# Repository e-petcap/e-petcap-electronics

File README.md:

# e-petcap-electronics
a e-petcap electronics

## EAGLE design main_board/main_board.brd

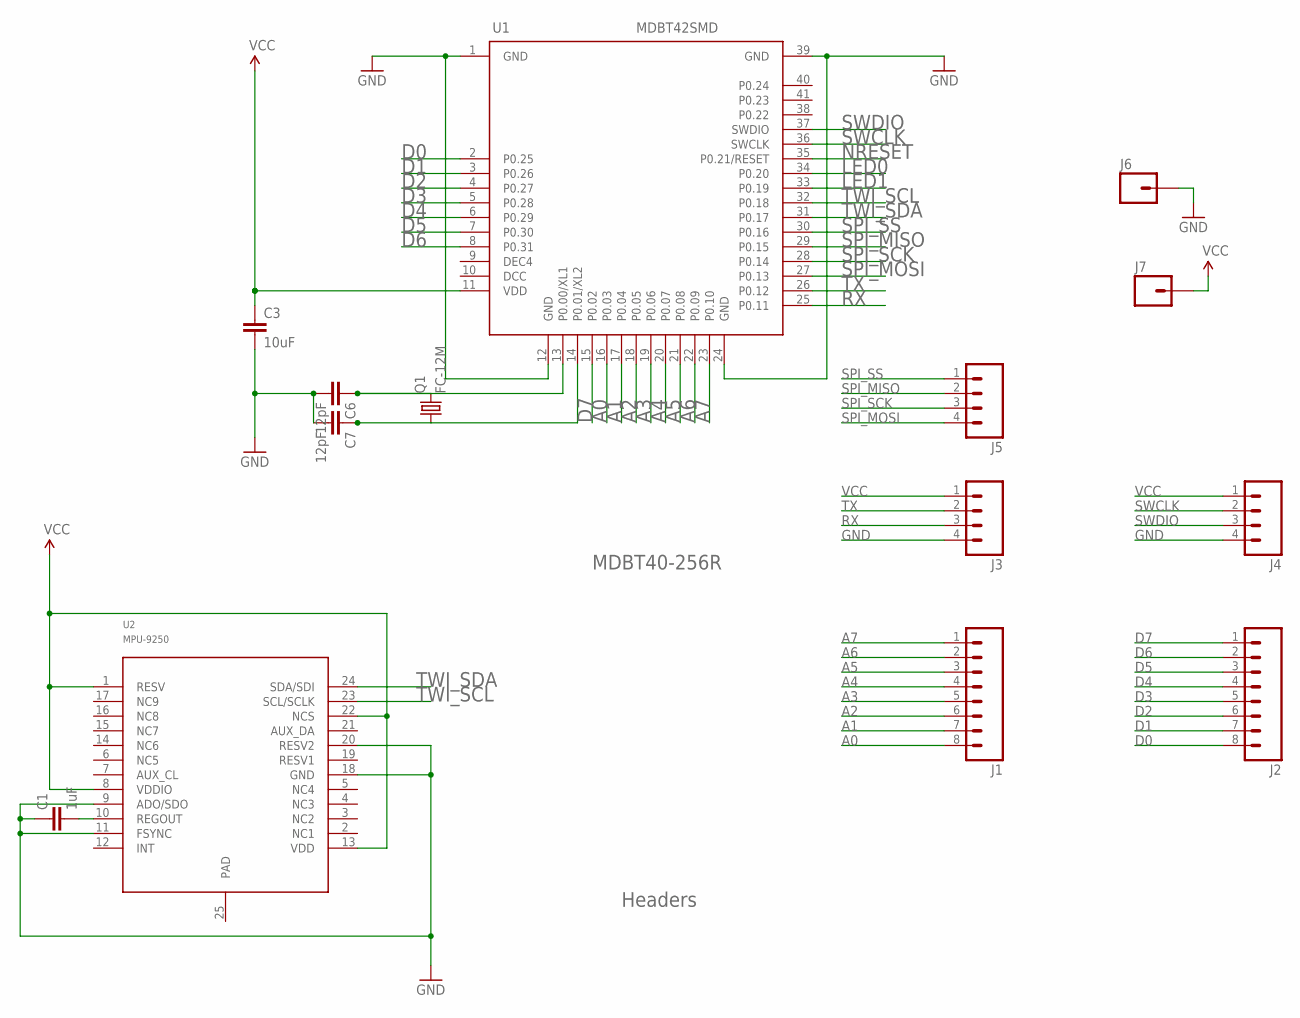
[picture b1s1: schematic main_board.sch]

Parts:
C1: 1uF; 0603-CAP
C3: 10uF; 0603-CAP
C6, C7: 12pF; 0603-CAP
J1, J2: M08SILK_FEMALE_PTH; 1X08
J3, J4, J5: M04PTH; 1X04
J6, J7: M01_SMDSMD_4X2; 1X01_SMD
Q1: FC-12M
U1: MDBT42SMD; MDBT42
U2: MPU-9250; LEAD-QFN24

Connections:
A0: J1.8, U1.16 (P0.03)
A1: J1.7, U1.17 (P0.04)
A2: J1.6, U1.18 (P0.05)
A3: J1.5, U1.19 (P0.06)
A4: J1.4, U1.20 (P0.07)
A5: J1.3, U1.21 (P0.08)
A6: J1.2, U1.22 (P0.09)
A7: J1.1, U1.23 (P0.10)
D0: J2.8, U1.2 (P0.25)
D1: J2.7, U1.3 (P0.26)
D2: J2.6, U1.4 (P0.27)
D3: J2.5, U1.5 (P0.28)
D4: J2.4, U1.6 (P0.29)
D5: J2.3, U1.7 (P0.30)
D6: J2.2, U1.8 (P0.31)
D7: J2.1, U1.15 (P0.02)
GND: C1.1, C3.2, C6.2, C7.2, J3.4, J4.4, J6.P$1, U1.1 (GND), U1.12 (GND), U1.24 (GND), U1.39 (GND), U2.9 (ADO/SDO), U2.11 (FSYNC), U2.18 (GND), U2.20 (RESV2)
LED0: U1.34 (P0.20)
LED1: U1.33 (P0.19)
unnamed: C7.1, Q1.1, U1.14 (P0.01/XL2)
unnamed: C6.1, Q1.2, U1.13 (P0.00/XL1)
unnamed: C1.2, U2.10 (REGOUT)
NRESET: U1.35 (P0.21/RESET)
RX: J3.3, U1.25 (P0.11)
SPI_MISO: J5.2, U1.29 (P0.15)
SPI_MOSI: J5.4, U1.27 (P0.13)
SPI_SCK: J5.3, U1.28 (P0.14)
SPI_SS: J5.1, U1.30 (P0.16)
SWCLK: J4.2, U1.36 (SWCLK)
SWDIO: J4.3, U1.37 (SWDIO)
TWI_SCL: U1.32 (P0.18), U2.23 (SCL/SCLK)
TWI_SDA: U1.31 (P0.17), U2.24 (SDA/SDI)
TX: J3.2, U1.26 (P0.12)
VCC: C3.1, J3.1, J4.1, J7.P$1, U1.11 (VDD), U2.1 (RESV), U2.8 (VDDIO), U2.13 (VDD), U2.22 (NCS)

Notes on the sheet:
Headers
MDBT40-256R

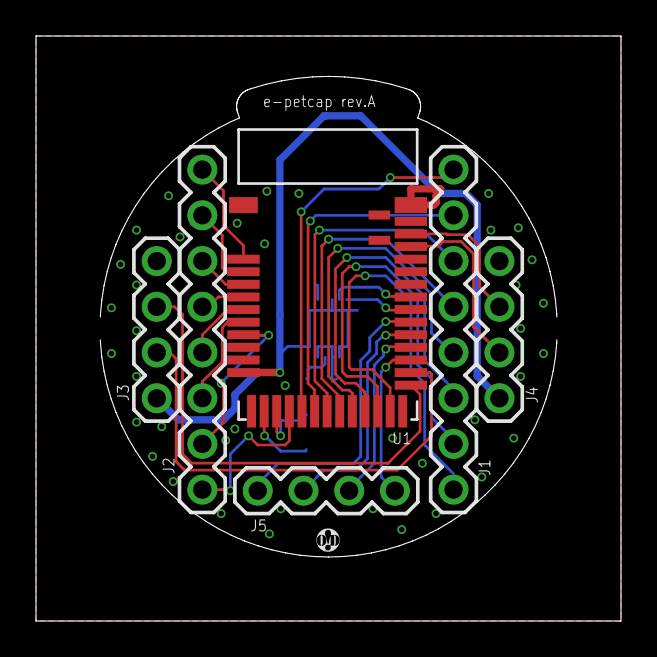
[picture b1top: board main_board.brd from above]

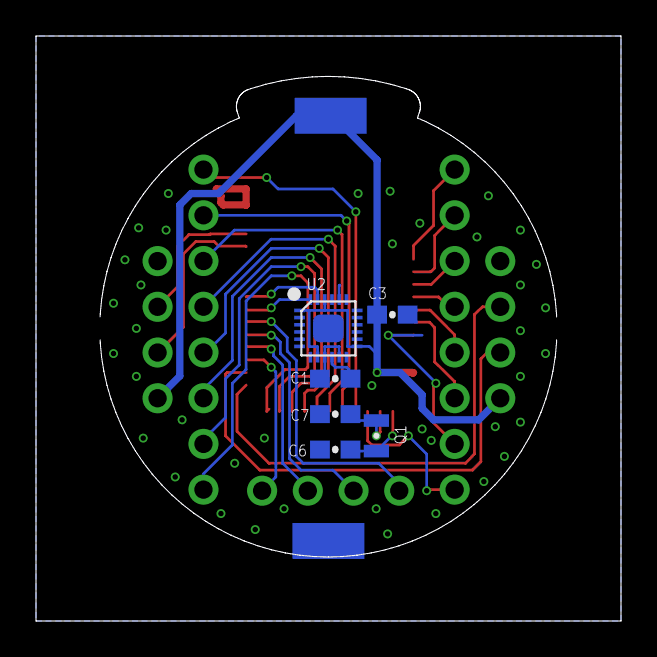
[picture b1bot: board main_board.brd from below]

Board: 4 copper layers, 32.5 x 32.5 mm, 14 parts (8 on the bottom side), 31 nets.

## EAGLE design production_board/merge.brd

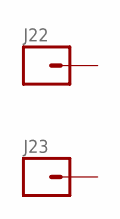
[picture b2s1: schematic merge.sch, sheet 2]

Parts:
J22, J23: M01; 1X01_BIG

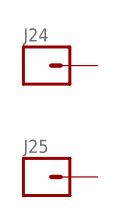
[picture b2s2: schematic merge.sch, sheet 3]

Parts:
J24, J25: M01; 1X01_BIG

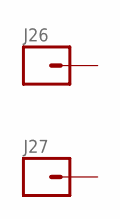
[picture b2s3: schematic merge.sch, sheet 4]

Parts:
J26, J27: M01; 1X01_BIG

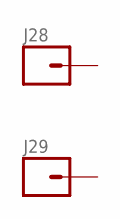
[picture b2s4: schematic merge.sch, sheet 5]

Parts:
J28, J29: M01; 1X01_BIG

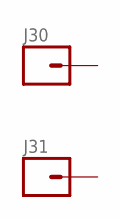
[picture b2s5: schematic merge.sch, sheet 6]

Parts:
J30, J31: M01; 1X01_BIG

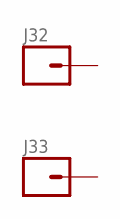
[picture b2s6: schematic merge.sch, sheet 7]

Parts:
J32, J33: M01; 1X01_BIG

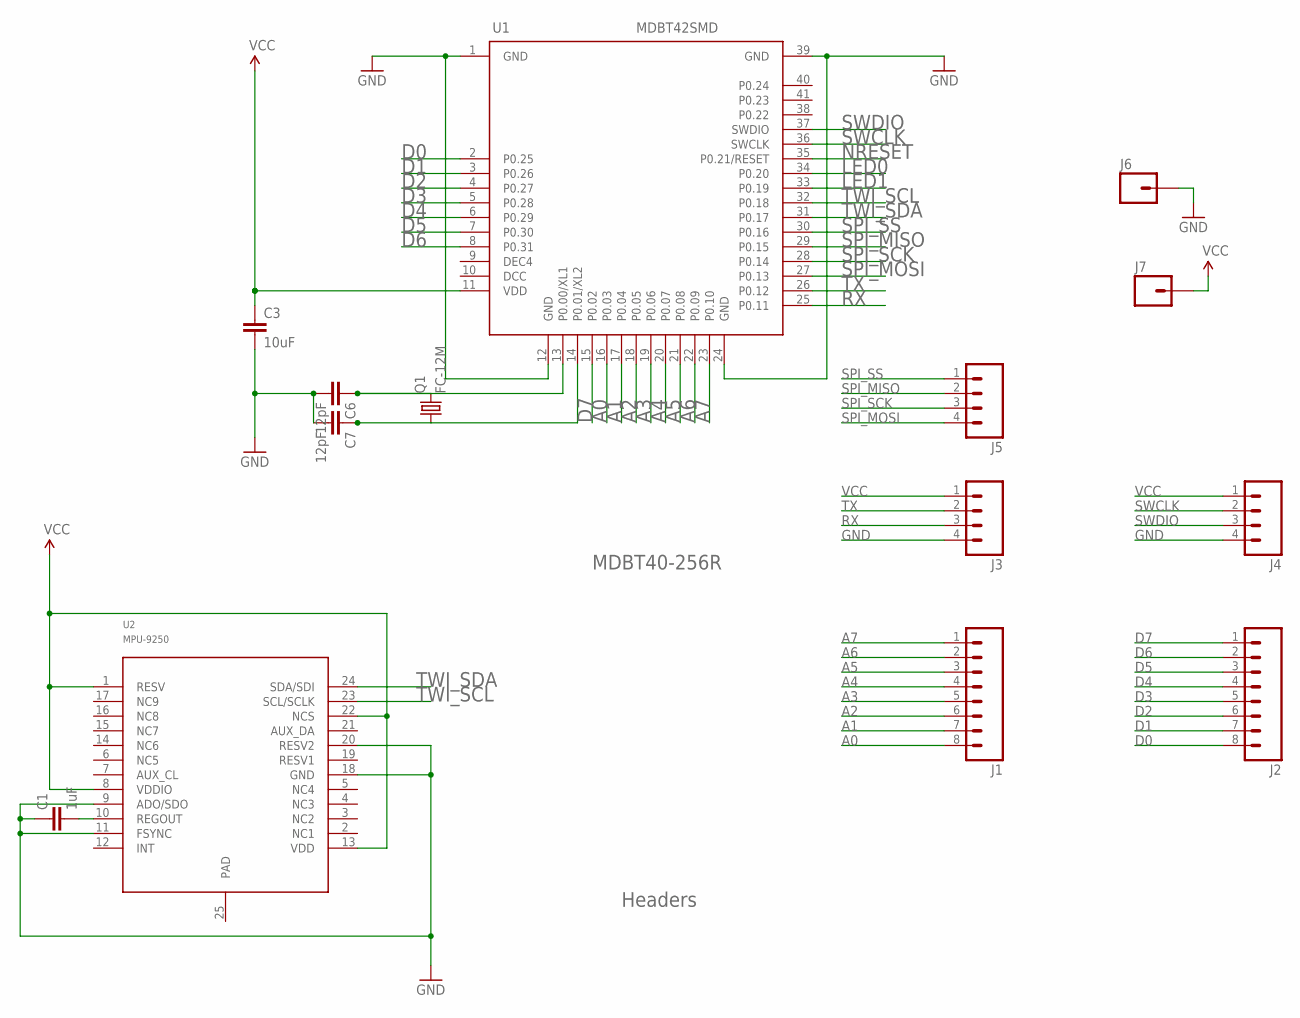
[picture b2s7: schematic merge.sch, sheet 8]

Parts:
C1: 1uF; 0603-CAP
C3: 10uF; 0603-CAP
C6, C7: 12pF; 0603-CAP
J1, J2: M08SILK_FEMALE_PTH; 1X08
J3, J4, J5: M04PTH; 1X04
J6, J7: M01_SMDSMD_4X2; 1X01_SMD
Q1: FC-12M
U1: MDBT42SMD; MDBT42
U2: MPU-9250; LEAD-QFN24

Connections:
A0: J1.8, U1.16 (P0.03); also elsewhere on the board
A1: J1.7, U1.17 (P0.04); also elsewhere on the board
A2: J1.6, U1.18 (P0.05); also elsewhere on the board
A3: J1.5, U1.19 (P0.06); also elsewhere on the board
A4: J1.4, U1.20 (P0.07); also elsewhere on the board
A5: J1.3, U1.21 (P0.08); also elsewhere on the board
A6: J1.2, U1.22 (P0.09); also elsewhere on the board
A7: J1.1, U1.23 (P0.10); also elsewhere on the board
D0: J2.8, U1.2 (P0.25); also elsewhere on the board
D1: J2.7, U1.3 (P0.26); also elsewhere on the board
D2: J2.6, U1.4 (P0.27); also elsewhere on the board
D3: J2.5, U1.5 (P0.28); also elsewhere on the board
D4: J2.4, U1.6 (P0.29); also elsewhere on the board
D5: J2.3, U1.7 (P0.30); also elsewhere on the board
D6: J2.2, U1.8 (P0.31); also elsewhere on the board
D7: J2.1, U1.15 (P0.02); also elsewhere on the board
GND: C1.1, C3.2, C6.2, C7.2, J3.4, J4.4, J6.P$1, U1.1 (GND), U1.12 (GND), U1.24 (GND), U1.39 (GND), U2.9 (ADO/SDO), U2.11 (FSYNC), U2.18 (GND), U2.20 (RESV2); also elsewhere on the board
LED0: U1.34 (P0.20); also elsewhere on the board
LED1: U1.33 (P0.19); also elsewhere on the board
unnamed: C7.1, Q1.1, U1.14 (P0.01/XL2)
unnamed: C6.1, Q1.2, U1.13 (P0.00/XL1)
unnamed: C1.2, U2.10 (REGOUT)
NRESET: U1.35 (P0.21/RESET); also elsewhere on the board
RX: J3.3, U1.25 (P0.11); also elsewhere on the board
SPI_MISO: J5.2, U1.29 (P0.15); also elsewhere on the board
SPI_MOSI: J5.4, U1.27 (P0.13); also elsewhere on the board
SPI_SCK: J5.3, U1.28 (P0.14); also elsewhere on the board
SPI_SS: J5.1, U1.30 (P0.16); also elsewhere on the board
SWCLK: J4.2, U1.36 (SWCLK); also elsewhere on the board
SWDIO: J4.3, U1.37 (SWDIO); also elsewhere on the board
TWI_SCL: U1.32 (P0.18), U2.23 (SCL/SCLK); also elsewhere on the board
TWI_SDA: U1.31 (P0.17), U2.24 (SDA/SDI); also elsewhere on the board
TX: J3.2, U1.26 (P0.12); also elsewhere on the board
VCC: C3.1, J3.1, J4.1, J7.P$1, U1.11 (VDD), U2.1 (RESV), U2.8 (VDDIO), U2.13 (VDD), U2.22 (NCS); also elsewhere on the board

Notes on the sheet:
Headers
MDBT40-256R

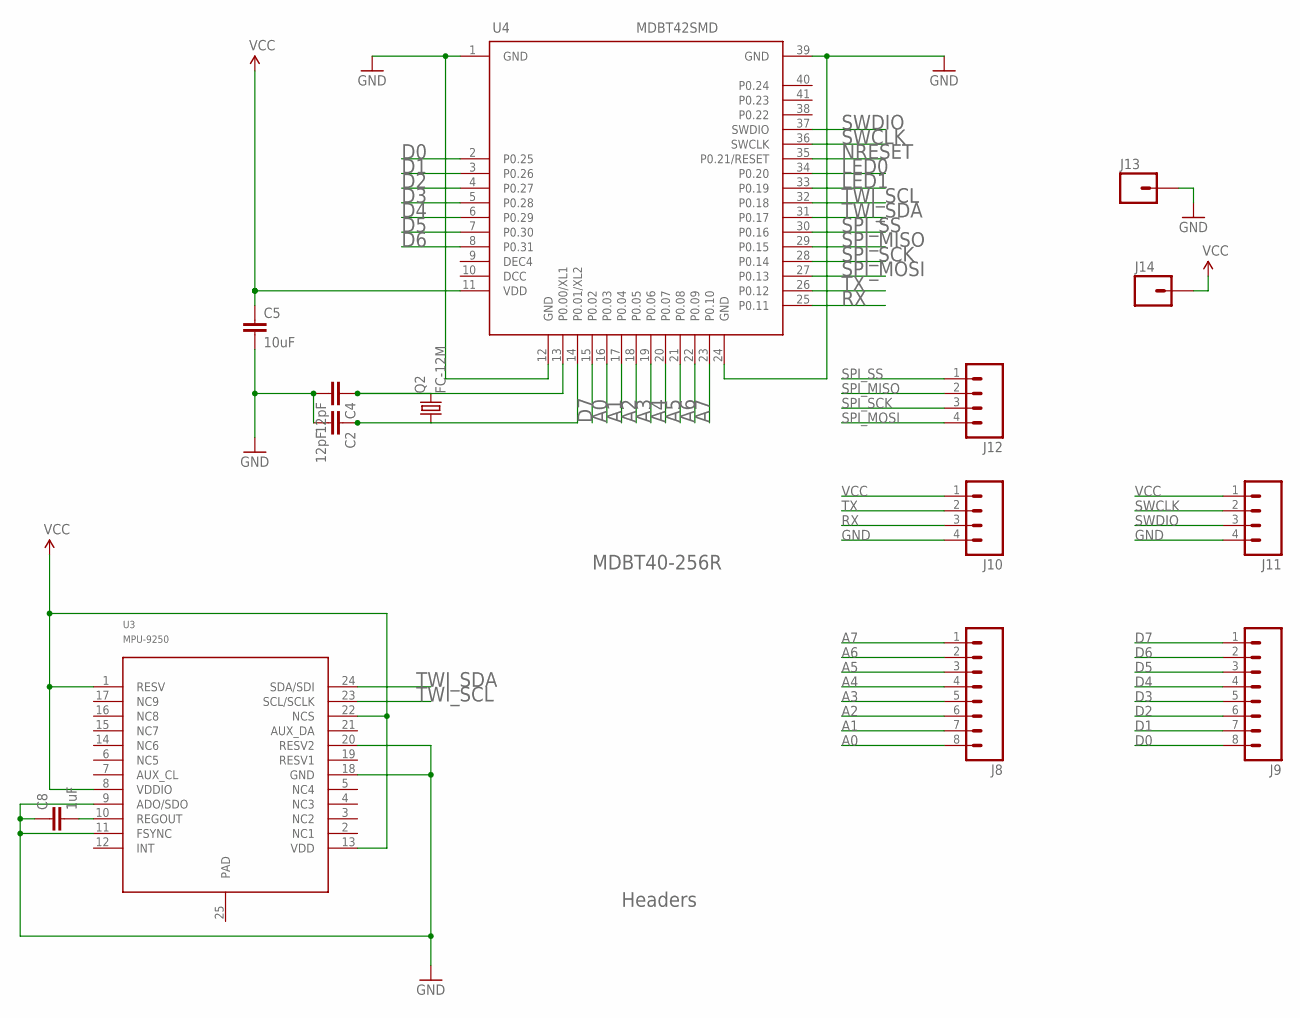
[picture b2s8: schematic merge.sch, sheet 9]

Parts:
C2, C4: 12pF; 0603-CAP
C5: 10uF; 0603-CAP
C8: 1uF; 0603-CAP
J8, J9: M08SILK_FEMALE_PTH; 1X08
J10, J11, J12: M04PTH; 1X04
J13, J14: M01_SMDSMD_4X2; 1X01_SMD
Q2: FC-12M
U3: MPU-9250; LEAD-QFN24
U4: MDBT42SMD; MDBT42

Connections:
A0: J8.8, U4.16 (P0.03); also elsewhere on the board
A1: J8.7, U4.17 (P0.04); also elsewhere on the board
A2: J8.6, U4.18 (P0.05); also elsewhere on the board
A3: J8.5, U4.19 (P0.06); also elsewhere on the board
A4: J8.4, U4.20 (P0.07); also elsewhere on the board
A5: J8.3, U4.21 (P0.08); also elsewhere on the board
A6: J8.2, U4.22 (P0.09); also elsewhere on the board
A7: J8.1, U4.23 (P0.10); also elsewhere on the board
D0: J9.8, U4.2 (P0.25); also elsewhere on the board
D1: J9.7, U4.3 (P0.26); also elsewhere on the board
D2: J9.6, U4.4 (P0.27); also elsewhere on the board
D3: J9.5, U4.5 (P0.28); also elsewhere on the board
D4: J9.4, U4.6 (P0.29); also elsewhere on the board
D5: J9.3, U4.7 (P0.30); also elsewhere on the board
D6: J9.2, U4.8 (P0.31); also elsewhere on the board
D7: J9.1, U4.15 (P0.02); also elsewhere on the board
GND: C2.2, C4.2, C5.2, C8.1, J10.4, J11.4, J13.P$1, U3.9 (ADO/SDO), U3.11 (FSYNC), U3.18 (GND), U3.20 (RESV2), U4.1 (GND), U4.12 (GND), U4.24 (GND), U4.39 (GND); also elsewhere on the board
LED0: U4.34 (P0.20); also elsewhere on the board
LED1: U4.33 (P0.19); also elsewhere on the board
unnamed: C2.1, Q2.1, U4.14 (P0.01/XL2)
unnamed: C4.1, Q2.2, U4.13 (P0.00/XL1)
unnamed: C8.2, U3.10 (REGOUT)
NRESET: U4.35 (P0.21/RESET); also elsewhere on the board
RX: J10.3, U4.25 (P0.11); also elsewhere on the board
SPI_MISO: J12.2, U4.29 (P0.15); also elsewhere on the board
SPI_MOSI: J12.4, U4.27 (P0.13); also elsewhere on the board
SPI_SCK: J12.3, U4.28 (P0.14); also elsewhere on the board
SPI_SS: J12.1, U4.30 (P0.16); also elsewhere on the board
SWCLK: J11.2, U4.36 (SWCLK); also elsewhere on the board
SWDIO: J11.3, U4.37 (SWDIO); also elsewhere on the board
TWI_SCL: U3.23 (SCL/SCLK), U4.32 (P0.18); also elsewhere on the board
TWI_SDA: U3.24 (SDA/SDI), U4.31 (P0.17); also elsewhere on the board
TX: J10.2, U4.26 (P0.12); also elsewhere on the board
VCC: C5.1, J10.1, J11.1, J14.P$1, U3.1 (RESV), U3.8 (VDDIO), U3.13 (VDD), U3.22 (NCS), U4.11 (VDD); also elsewhere on the board

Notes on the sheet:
Headers
MDBT40-256R

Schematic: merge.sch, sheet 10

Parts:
C9, C10: 12pF; 0603-CAP
C11: 10uF; 0603-CAP
C12: 1uF; 0603-CAP
J15, J16: M08SILK_FEMALE_PTH; 1X08
J17, J18, J19: M04PTH; 1X04
J20, J21: M01_SMDSMD_4X2; 1X01_SMD
Q3: FC-12M
U5: MPU-9250; LEAD-QFN24
U6: MDBT42SMD; MDBT42

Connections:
A0: J15.8, U6.16 (P0.03); also elsewhere on the board
A1: J15.7, U6.17 (P0.04); also elsewhere on the board
A2: J15.6, U6.18 (P0.05); also elsewhere on the board
A3: J15.5, U6.19 (P0.06); also elsewhere on the board
A4: J15.4, U6.20 (P0.07); also elsewhere on the board
A5: J15.3, U6.21 (P0.08); also elsewhere on the board
A6: J15.2, U6.22 (P0.09); also elsewhere on the board
A7: J15.1, U6.23 (P0.10); also elsewhere on the board
D0: J16.8, U6.2 (P0.25); also elsewhere on the board
D1: J16.7, U6.3 (P0.26); also elsewhere on the board
D2: J16.6, U6.4 (P0.27); also elsewhere on the board
D3: J16.5, U6.5 (P0.28); also elsewhere on the board
D4: J16.4, U6.6 (P0.29); also elsewhere on the board
D5: J16.3, U6.7 (P0.30); also elsewhere on the board
D6: J16.2, U6.8 (P0.31); also elsewhere on the board
D7: J16.1, U6.15 (P0.02); also elsewhere on the board
GND: C9.2, C10.2, C11.2, C12.1, J17.4, J18.4, J20.P$1, U5.9 (ADO/SDO), U5.11 (FSYNC), U5.18 (GND), U5.20 (RESV2), U6.1 (GND), U6.12 (GND), U6.24 (GND), U6.39 (GND); also elsewhere on the board
LED0: U6.34 (P0.20); also elsewhere on the board
LED1: U6.33 (P0.19); also elsewhere on the board
unnamed: C9.1, Q3.1, U6.14 (P0.01/XL2)
unnamed: C10.1, Q3.2, U6.13 (P0.00/XL1)
unnamed: C12.2, U5.10 (REGOUT)
NRESET: U6.35 (P0.21/RESET); also elsewhere on the board
RX: J17.3, U6.25 (P0.11); also elsewhere on the board
SPI_MISO: J19.2, U6.29 (P0.15); also elsewhere on the board
SPI_MOSI: J19.4, U6.27 (P0.13); also elsewhere on the board
SPI_SCK: J19.3, U6.28 (P0.14); also elsewhere on the board
SPI_SS: J19.1, U6.30 (P0.16); also elsewhere on the board
SWCLK: J18.2, U6.36 (SWCLK); also elsewhere on the board
SWDIO: J18.3, U6.37 (SWDIO); also elsewhere on the board
TWI_SCL: U5.23 (SCL/SCLK), U6.32 (P0.18); also elsewhere on the board
TWI_SDA: U5.24 (SDA/SDI), U6.31 (P0.17); also elsewhere on the board
TX: J17.2, U6.26 (P0.12); also elsewhere on the board
VCC: C11.1, J17.1, J18.1, J21.P$1, U5.1 (RESV), U5.8 (VDDIO), U5.13 (VDD), U5.22 (NCS), U6.11 (VDD); also elsewhere on the board

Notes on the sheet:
Headers
MDBT40-256R

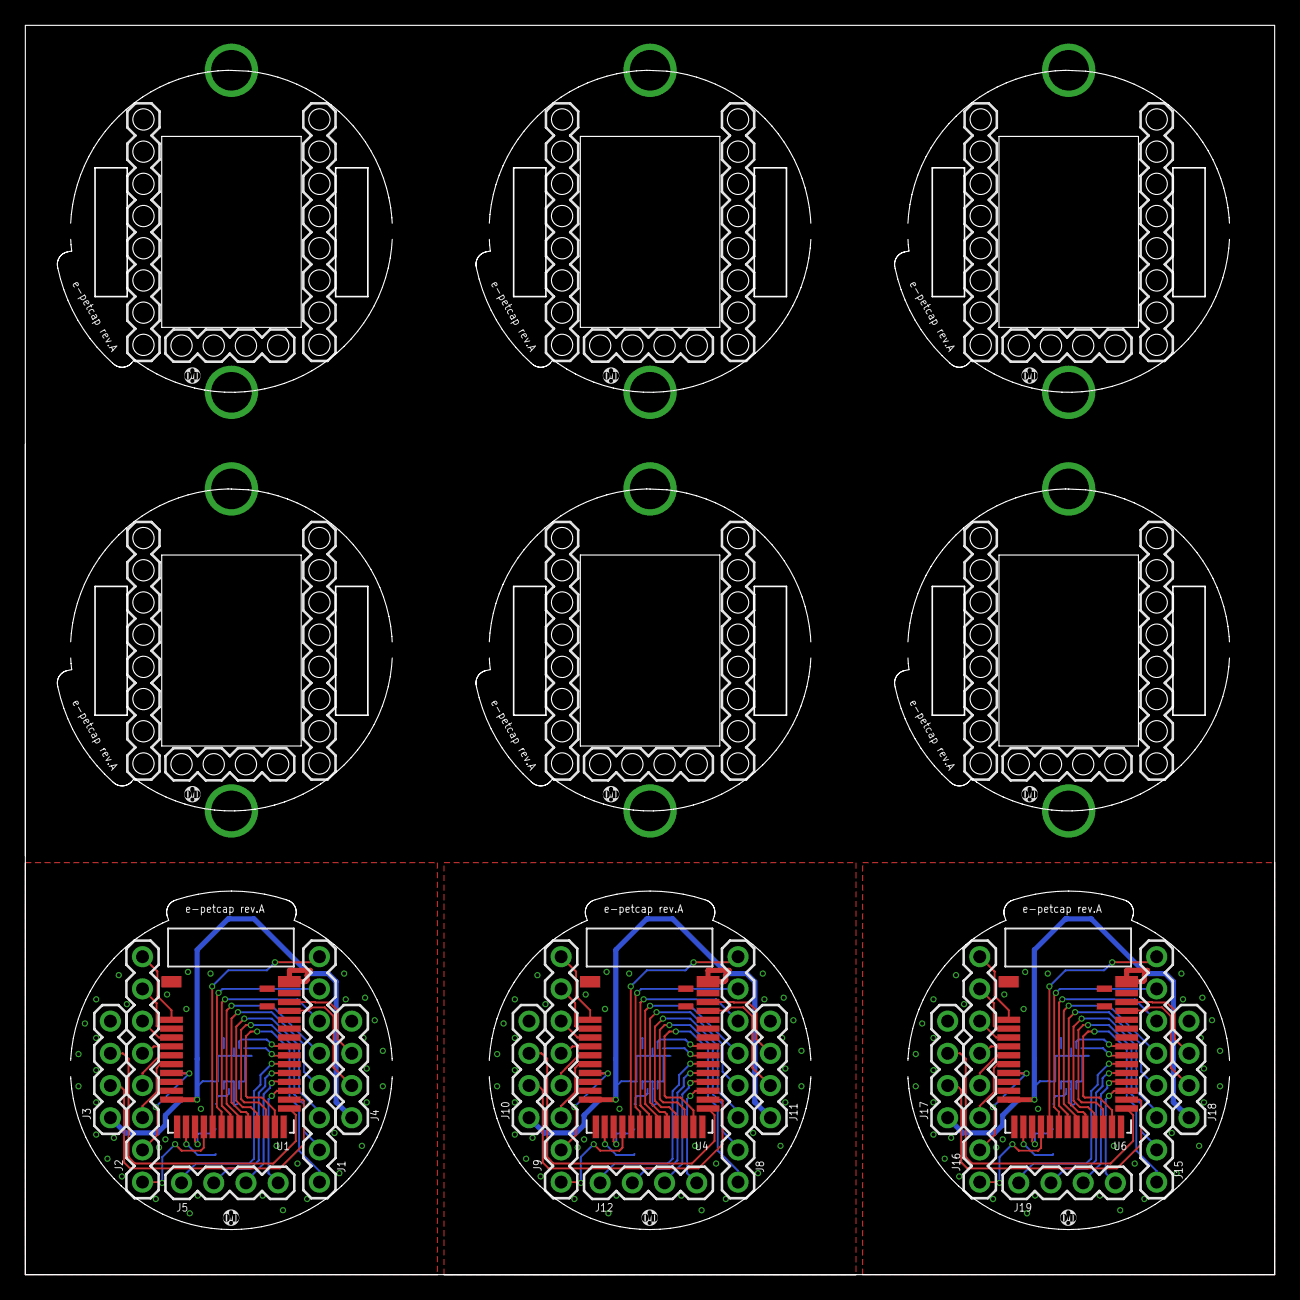
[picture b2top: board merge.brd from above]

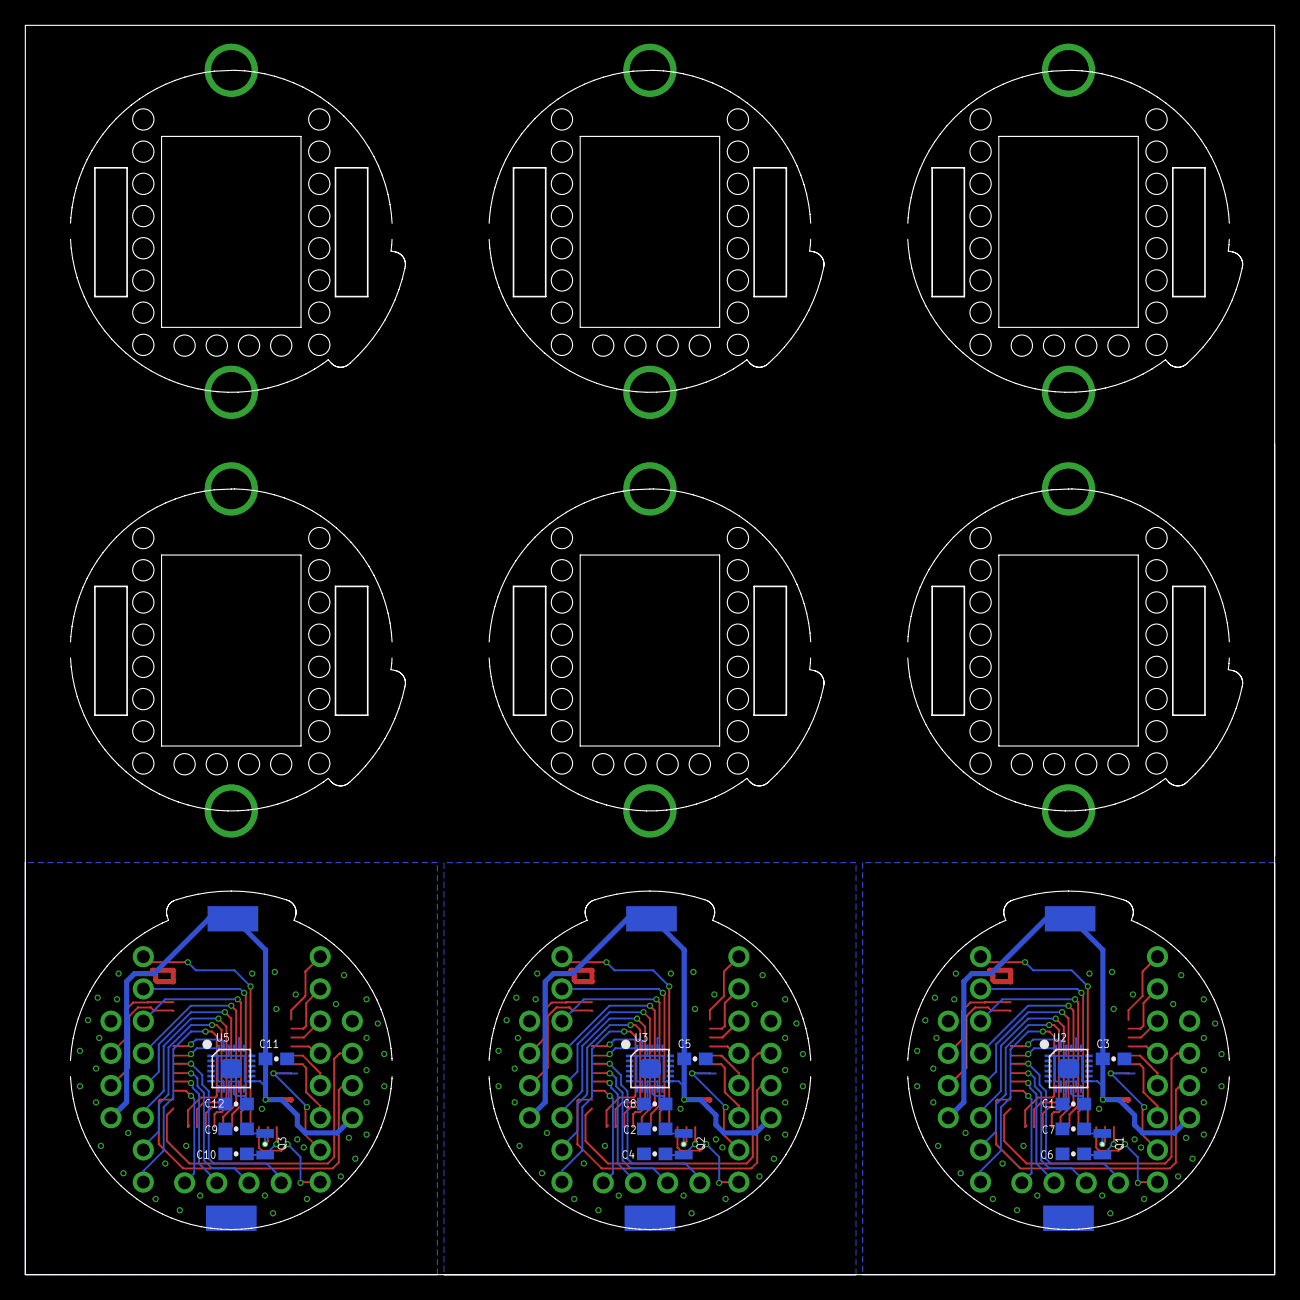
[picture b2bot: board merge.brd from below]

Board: 4 copper layers, 98.5 x 98.5 mm, 84 parts (24 on the bottom side), 40 nets.

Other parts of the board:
U$1, U$2, U$6, U$7, U$11, U$12, U$16, U$17, U$21, U$22, U$26, U$27: 1X04_SPACER
U$3, U$8, U$13, U$18, U$23, U$28: 1X04_HOLE
U$4, U$5, U$9, U$10, U$14, U$15, U$19, U$20, U$24, U$25, U$29, U$30: 1X08_HOLE

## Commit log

2016-09-11 .project
2016-10-05 for fist prototype
2016-10-05 MDBT42
2016-10-06 before order r2 board

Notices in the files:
parts and their libraries:
SparkFun-Capacitors: Licensing: Creative Commons ShareAlike 4.0 International - https://creativecommons.org/licenses/by-sa/4.0
